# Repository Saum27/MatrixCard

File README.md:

# MatrixCard

|  |  |
| :-------------------------------------------------------: | :----------------------------------------------------: |

## What is it?

The MatrixCard is a basic engineering project I made for school. It is an LED matrix with microcontroller designed to fit in the form factor of a credit card.

### Technical Specifications

- MCU: Seeed Studio XIAO RP2040
- Matrix Controller: Lumissil IS31FL3731 (QFN-28)
- Resolution: 16x9 monochrome
- PCB copper layers: 2
- Dimensions: 85.60 x 53.98 millimeters
- SMD footprints: 0603 (1608 metric)

## But why?????

IDK I thought it would be cool. I also wanted to learn PCB design with KiCAD, this being my first completed project using the software. I also wanted to learn the basics in how to use Git, which I already knew how to use, but had not used in a personal project.

## Can **_I_** make one?????

Of course! I wanted to make this project open source both to showcase it and to allow those who want to iterate on it or just build it themselves to do so.

### Parts needed

Some extra parts are needed. It should be noted that the LEDs listed give enough for 2 MatrixCards, and that the variety pack of SMD components has many extraneous components that are not necessarily needed for assembly. Consult the schematic for resistor and capacitor values.

| part                          | link |
| :---------------------------: | :---------------------------------------------------------------------------------------------------------------: |
| Seeed Studio Xiao RP2040      | [link](https://www.seeedstudio.com/XIAO-RP2040-v1-0-p-5026.html)                                                  |
| Lumissil IS31FL3731           | [link](https://www.digikey.com/en/products/detail/lumissil-microsystems/IS31FL3731-QFLS2-TR/4286473)              |
| 0603 SMD Components (variety) | [link](https://www.amazon.com/0603-Capacitors-Transistors-Electronic-Book/dp/B0B2ZRPCSF?crid=26EKNK0BXYP7U)       |
| 0603 SMD LEDs (300x, blue)    | [link](https://www.amazon.com/uxcell-Lights-Electronics-Components-Emitting/dp/B07DLBC43V?crid=JFB5RWVKTOGE)      |

### Required tools

Some tools are required if you want to build your own MatrixCard.

- Soldering iron
- Solder
- Solder Paste and Stencil (recommended)
- Solder Flux (recommended)
- Hot-air rework station (recommended)

## To Do

- [ ] add (more) images
- [x] add schematic PDF
- [x] add missing information
- [ ] add Arduino sketch
- [ ] create issues for each entry on this list

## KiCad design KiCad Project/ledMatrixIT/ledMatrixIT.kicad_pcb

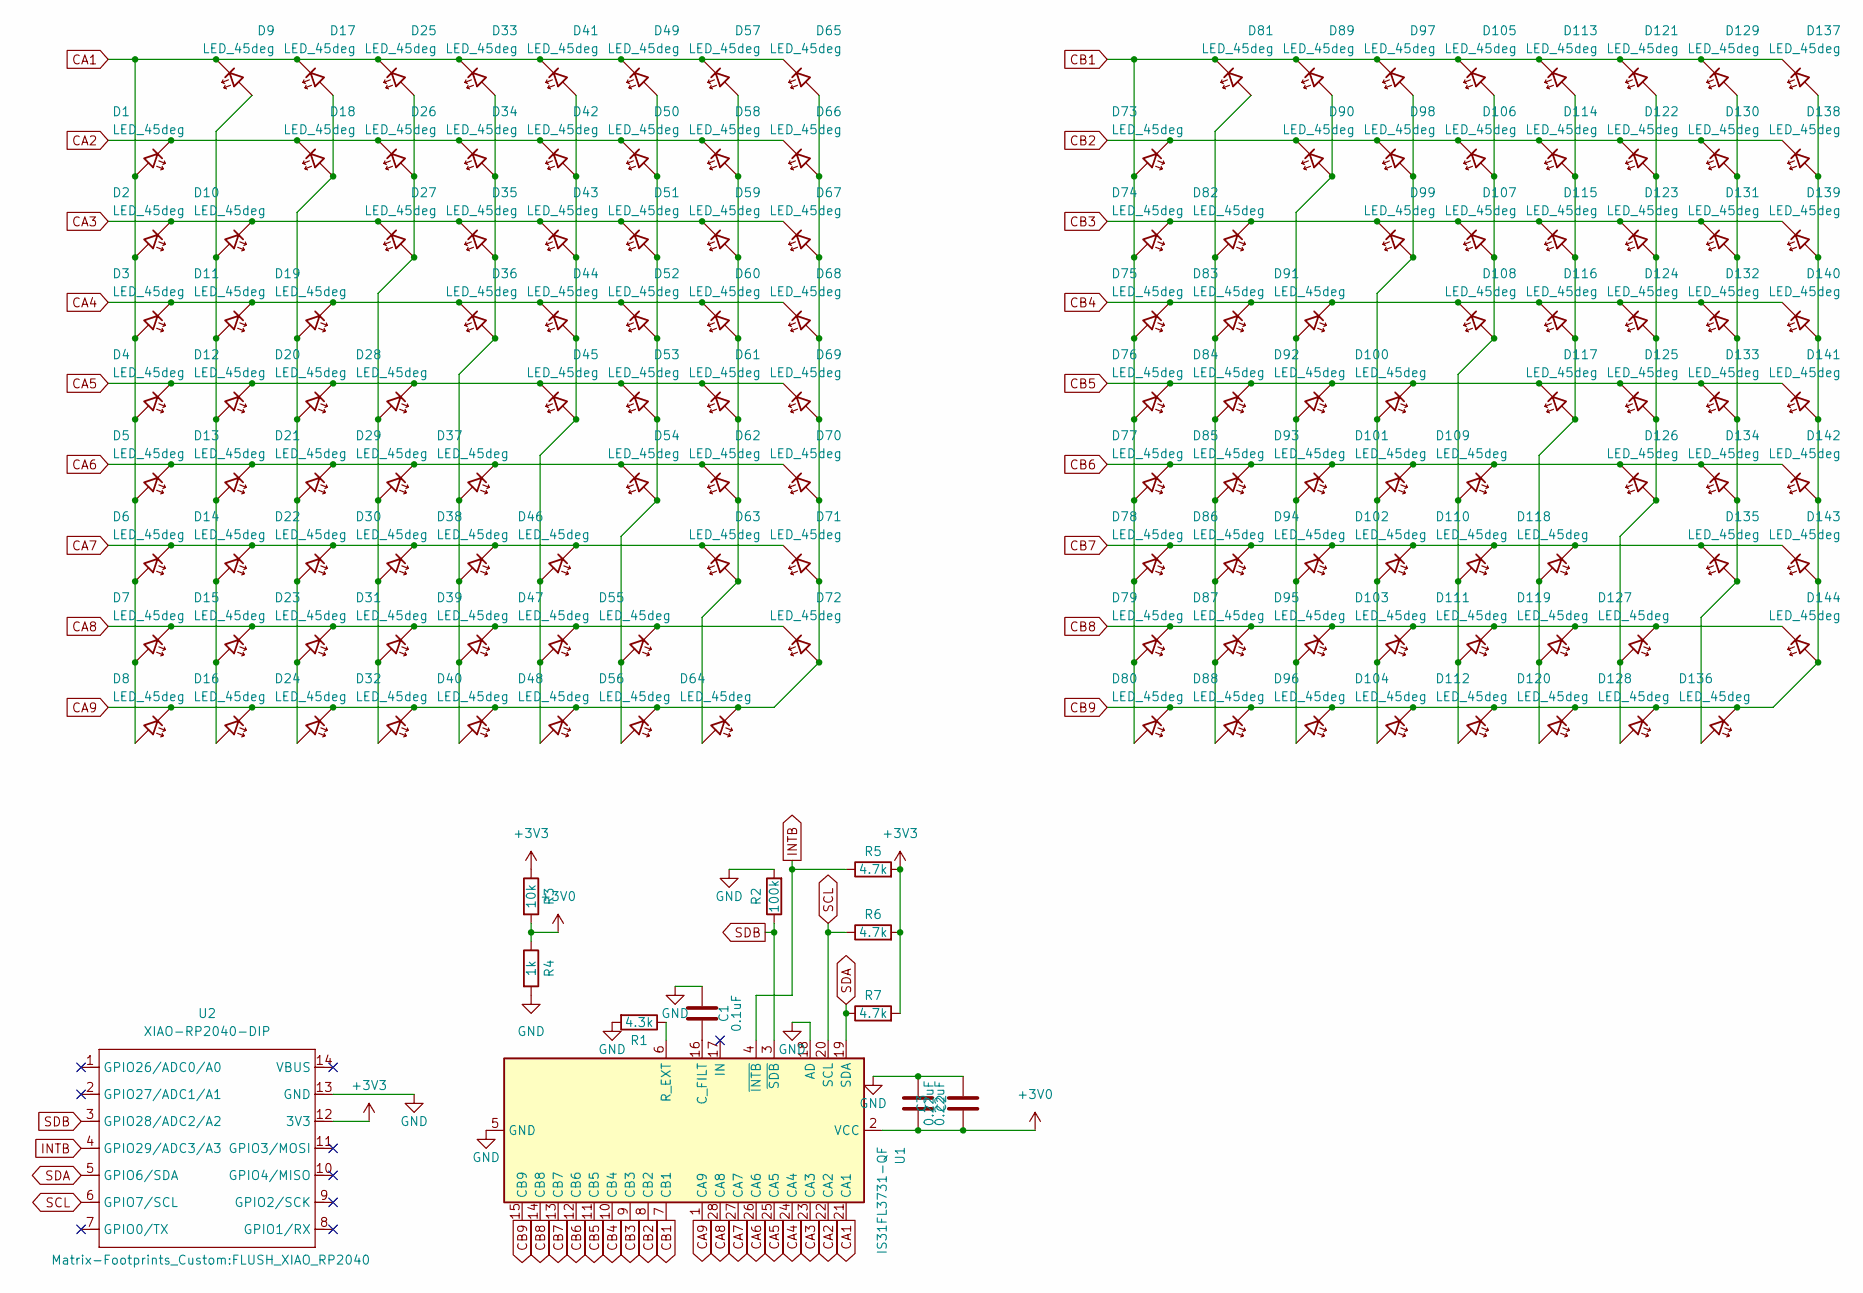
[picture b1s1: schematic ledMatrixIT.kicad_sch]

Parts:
C1: 0.1uF; 0603_CAP
C2, C3: 0.22uF; 0603_CAP
D1, D2, D3, D4, D5, D6, D7, D8, D9, D10, D11, D12, D13, D14, D15, D16, D17, D18, D19, D20, D21, D22, D23, D24, D25, D26, D27, D28, D29, D30, D31, D32, D33, D34, D35, D36, D37, D38, D39, D40, D41, D42, D43, D44, D45, D46, D47, D48, D49, D50, D51, D52, D53, D54, D55, D56, D57, D58, D59, D60, D61, D62, D63, D64, D65, D66, D67, D68, D69, D70, D71, D72, D73, D74, D75, D76, D77, D78, D79, D80, D81, D82, D83, D84, D85, D86, D87, D88, D89, D90, D91, D92, D93, D94, D95, D96, D97, D98, D99, D100, D101, D102, D103, D104, D105, D106, D107, D108, D109, D110, D111, D112, D113, D114, D115, D116, D117, D118, D119, D120, D121, D122, D123, D124, D125, D126, D127, D128, D129, D130, D131, D132, D133, D134, D135, D136, D137, D138, D139, D140, D141, D142, D143, D144: LED_45deg; 0603_LED
R1: 4.3k; 0603_RES
R2: 100k; 0603_RES
R3: 10k; 0603_RES
R4: 1k; 0603_RES
R5, R6, R7: 4.7k; 0603_RES
U1: IS31FL3731-QF; IS31FL3731
U2: XIAO-RP2040-DIP; FLUSH_XIAO_RP2040

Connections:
+3V0: C2.2, C3.1, R3.2, R4.1, U1.2 (VCC)
+3V3: R3.1, R5.2, R6.2, R7.2, U2.12 (3V3)
CA1: D1.2 (A), D2.2 (A), D3.2 (A), D4.2 (A), D5.2 (A), D6.2 (A), D7.2 (A), D8.2 (A), D9.1 (K), D17.1 (K), D25.1 (K), D33.1 (K), D41.1 (K), D49.1 (K), D57.1 (K), D65.1 (K), U1.21 (CA1)
CA2: D1.1 (K), D18.1 (K), D26.1 (K), D34.1 (K), D42.1 (K), D50.1 (K), D58.1 (K), D66.1 (K), U1.22 (CA2)
CA3: D2.1 (K), D10.1 (K), D27.1 (K), D35.1 (K), D43.1 (K), D51.1 (K), D59.1 (K), D67.1 (K), U1.23 (CA3)
CA4: D3.1 (K), D11.1 (K), D19.1 (K), D36.1 (K), D44.1 (K), D52.1 (K), D60.1 (K), D68.1 (K), U1.24 (CA4)
CA5: D4.1 (K), D12.1 (K), D20.1 (K), D28.1 (K), D45.1 (K), D53.1 (K), D61.1 (K), D69.1 (K), U1.25 (CA5)
CA6: D5.1 (K), D13.1 (K), D21.1 (K), D29.1 (K), D37.1 (K), D54.1 (K), D62.1 (K), D70.1 (K), U1.26 (CA6)
CA7: D6.1 (K), D14.1 (K), D22.1 (K), D30.1 (K), D38.1 (K), D46.1 (K), D63.1 (K), D71.1 (K), U1.27 (CA7)
CA8: D7.1 (K), D15.1 (K), D23.1 (K), D31.1 (K), D39.1 (K), D47.1 (K), D55.1 (K), D72.1 (K), U1.28 (CA8)
CA9: D8.1 (K), D16.1 (K), D24.1 (K), D32.1 (K), D40.1 (K), D48.1 (K), D56.1 (K), D64.1 (K), D65.2 (A), D66.2 (A), D67.2 (A), D68.2 (A), D69.2 (A), D70.2 (A), D71.2 (A), D72.2 (A), U1.1 (CA9)
CB1: D73.2 (A), D74.2 (A), D75.2 (A), D76.2 (A), D77.2 (A), D78.2 (A), D79.2 (A), D80.2 (A), D81.1 (K), D89.1 (K), D97.1 (K), D105.1 (K), D113.1 (K), D121.1 (K), D129.1 (K), D137.1 (K), U1.7 (CB1)
CB2: D73.1 (K), D90.1 (K), D98.1 (K), D106.1 (K), D114.1 (K), D122.1 (K), D130.1 (K), D138.1 (K), U1.8 (CB2)
CB3: D74.1 (K), D82.1 (K), D99.1 (K), D107.1 (K), D115.1 (K), D123.1 (K), D131.1 (K), D139.1 (K), U1.9 (CB3)
CB4: D75.1 (K), D83.1 (K), D91.1 (K), D108.1 (K), D116.1 (K), D124.1 (K), D132.1 (K), D140.1 (K), U1.10 (CB4)
CB5: D76.1 (K), D84.1 (K), D92.1 (K), D100.1 (K), D117.1 (K), D125.1 (K), D133.1 (K), D141.1 (K), U1.11 (CB5)
CB6: D77.1 (K), D85.1 (K), D93.1 (K), D101.1 (K), D109.1 (K), D126.1 (K), D134.1 (K), D142.1 (K), U1.12 (CB6)
CB7: D78.1 (K), D86.1 (K), D94.1 (K), D102.1 (K), D110.1 (K), D118.1 (K), D135.1 (K), D143.1 (K), U1.13 (CB7)
CB8: D79.1 (K), D87.1 (K), D95.1 (K), D103.1 (K), D111.1 (K), D119.1 (K), D127.1 (K), D144.1 (K), U1.14 (CB8)
CB9: D80.1 (K), D88.1 (K), D96.1 (K), D104.1 (K), D112.1 (K), D120.1 (K), D128.1 (K), D136.1 (K), D137.2 (A), D138.2 (A), D139.2 (A), D140.2 (A), D141.2 (A), D142.2 (A), D143.2 (A), D144.2 (A), U1.15 (CB9)
GND: C1.2, C2.1, C3.2, R1.2, R2.2, R4.2, U1.5 (GND), U1.18 (AD), U1.29 (GND), U2.13 (GND)
INTB: R5.1, U1.4 (~INTB), U2.4 (GPIO29/ADC3/A3)
unnamed: D9.2 (A), D10.2 (A), D11.2 (A), D12.2 (A), D13.2 (A), D14.2 (A), D15.2 (A), D16.2 (A)
unnamed: D17.2 (A), D18.2 (A), D19.2 (A), D20.2 (A), D21.2 (A), D22.2 (A), D23.2 (A), D24.2 (A)
unnamed: D25.2 (A), D26.2 (A), D27.2 (A), D28.2 (A), D29.2 (A), D30.2 (A), D31.2 (A), D32.2 (A)
unnamed: D33.2 (A), D34.2 (A), D35.2 (A), D36.2 (A), D37.2 (A), D38.2 (A), D39.2 (A), D40.2 (A)
unnamed: D41.2 (A), D42.2 (A), D43.2 (A), D44.2 (A), D45.2 (A), D46.2 (A), D47.2 (A), D48.2 (A)
unnamed: D49.2 (A), D50.2 (A), D51.2 (A), D52.2 (A), D53.2 (A), D54.2 (A), D55.2 (A), D56.2 (A)
unnamed: D57.2 (A), D58.2 (A), D59.2 (A), D60.2 (A), D61.2 (A), D62.2 (A), D63.2 (A), D64.2 (A)
unnamed: D81.2 (A), D82.2 (A), D83.2 (A), D84.2 (A), D85.2 (A), D86.2 (A), D87.2 (A), D88.2 (A)
unnamed: D89.2 (A), D90.2 (A), D91.2 (A), D92.2 (A), D93.2 (A), D94.2 (A), D95.2 (A), D96.2 (A)
unnamed: D97.2 (A), D98.2 (A), D99.2 (A), D100.2 (A), D101.2 (A), D102.2 (A), D103.2 (A), D104.2 (A)
unnamed: D105.2 (A), D106.2 (A), D107.2 (A), D108.2 (A), D109.2 (A), D110.2 (A), D111.2 (A), D112.2 (A)
unnamed: D113.2 (A), D114.2 (A), D115.2 (A), D116.2 (A), D117.2 (A), D118.2 (A), D119.2 (A), D120.2 (A)
unnamed: D121.2 (A), D122.2 (A), D123.2 (A), D124.2 (A), D125.2 (A), D126.2 (A), D127.2 (A), D128.2 (A)
unnamed: D129.2 (A), D130.2 (A), D131.2 (A), D132.2 (A), D133.2 (A), D134.2 (A), D135.2 (A), D136.2 (A)
unnamed: C1.1, U1.16 (C_FILT)
unnamed: R1.1, U1.6 (R_EXT)
SCL: R6.1, U1.20 (SCL), U2.6 (GPIO7/SCL)
SDA: R7.1, U1.19 (SDA), U2.5 (GPIO6/SDA)
SDB: R2.1, U1.3 (~SDB), U2.3 (GPIO28/ADC2/A2)

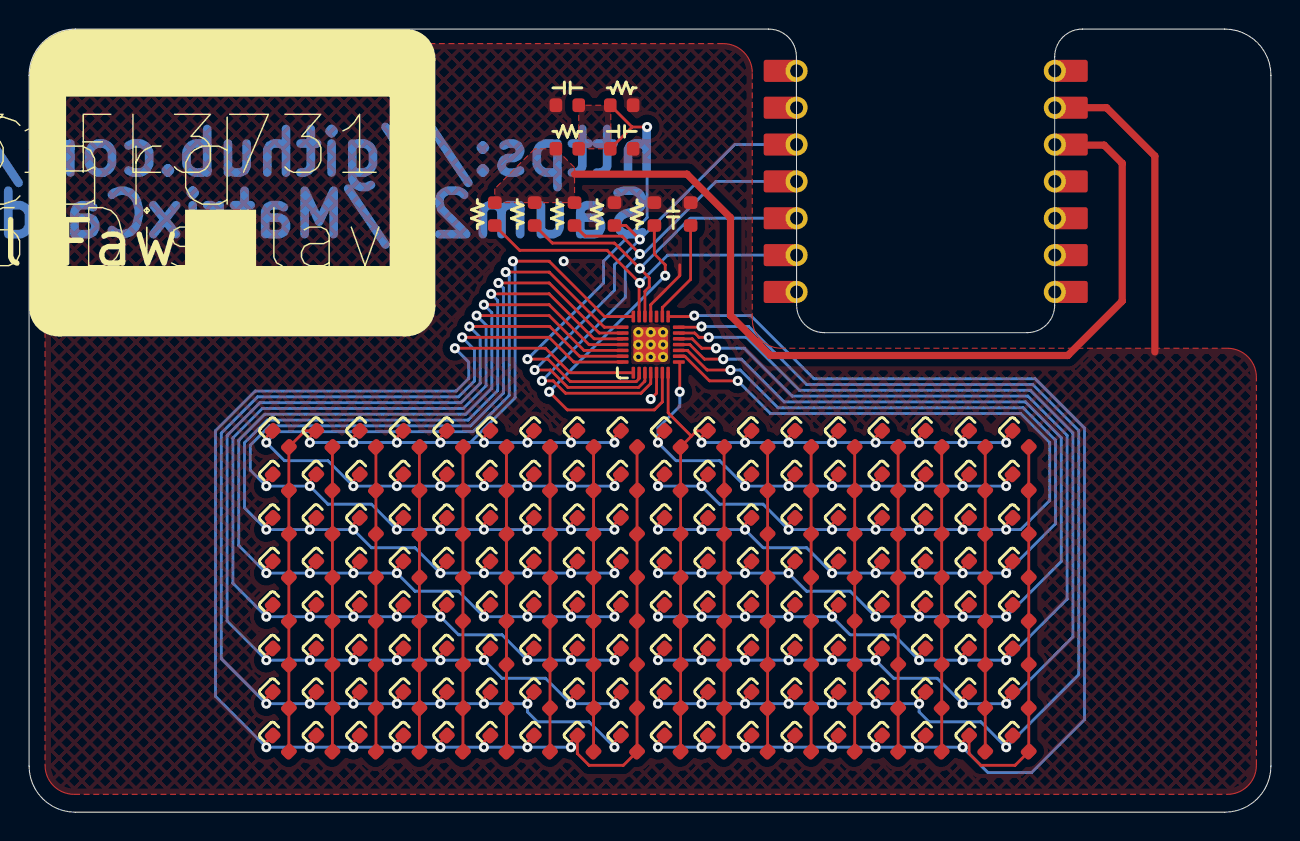
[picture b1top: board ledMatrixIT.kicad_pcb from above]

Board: 2 copper layers, 85.6 x 54.0 mm, 156 parts (0 on the bottom side), 41 nets.

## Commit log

2025-03-04 first commit - added all files
2025-03-05 Added front and rear render images
2025-03-05 added a couple of images and other edits to the README
2025-03-05 added task list
2025-03-05 added schematic pdf to images directory and improved schematic readability
2025-03-06 added missing board dimensions
2025-03-06 added 'add Arduino sketch' to 'Td Do' list
2025-03-07 turned the KiCad project into an archive and removed extraneous gerber packages
